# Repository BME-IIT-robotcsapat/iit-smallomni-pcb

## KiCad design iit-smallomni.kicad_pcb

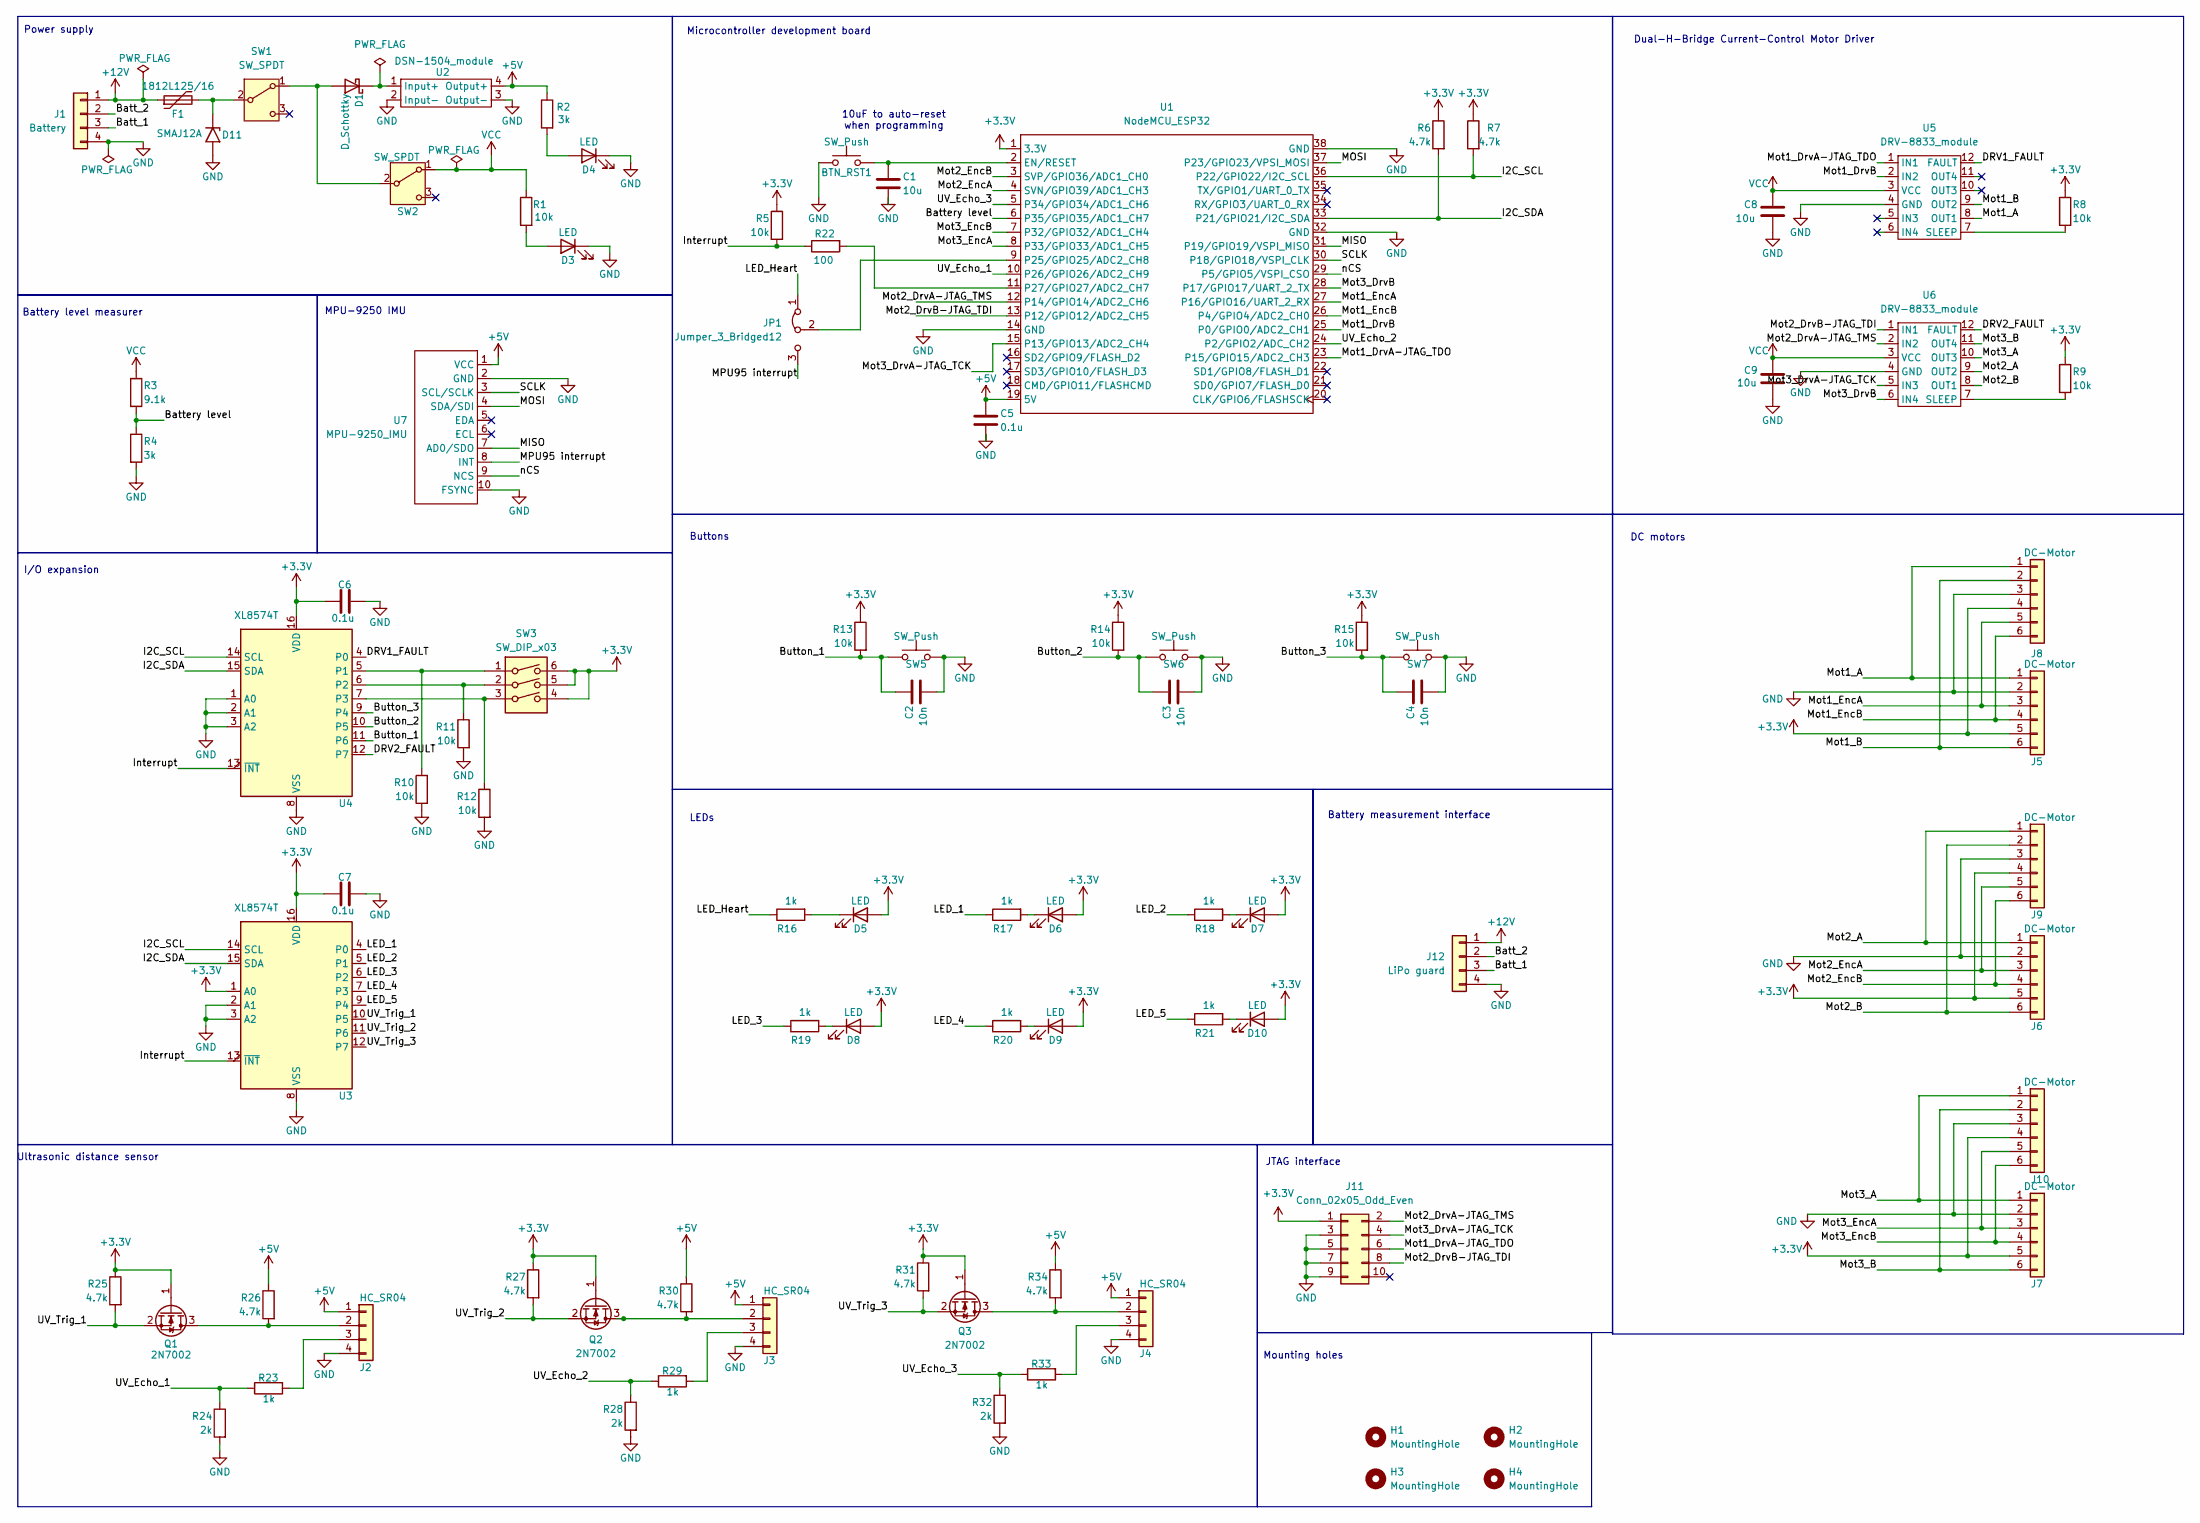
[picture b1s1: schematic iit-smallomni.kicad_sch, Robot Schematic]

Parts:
BTN_RST1: SW_Push; SW_PUSH_6mm_H5mm
C1, C8, C9: 10u; C_0805_2012Metric_Pad1.18x1.45mm_HandSolder
C2, C3, C4: 10n; C_0805_2012Metric_Pad1.18x1.45mm_HandSolder
C5, C6, C7: 0.1u; C_0805_2012Metric_Pad1.18x1.45mm_HandSolder
D1: D_Schottky; D_SOD-123FL
D3, D4, D5, D6, D7, D8, D9, D10: LED; LED_0805_2012Metric_Pad1.15x1.40mm_HandSolder
D11: SMAJ12A; D_SMA
F1: 1812L125/16; polyfuse
H1, H2, H3, H4: MountingHole; MountingHole_3.2mm_M3
J1: Battery; Molex_KK-254_AE-6410-04A_1x04_P2.54mm_Vertical
J2, J3, J4: HC_SR04; PinSocket_1x04_P2.54mm_Vertical
J5, J6, J7: DC-Motor; Molex_KK-254_AE-6410-06A_1x06_P2.54mm_Vertical
J8, J9, J10: DC-Motor; legacy-motor
J11: Conn_02x05_Odd_Even; IDC-Header_2x05_P2.54mm_Vertical
J12: LiPo guard; PinSocket_1x04_P2.54mm_Vertical
JP1: Jumper_3_Bridged12; PinHeader_1x03_P2.54mm_Vertical
Q1, Q2, Q3: 2N7002; SOT-23
R1, R5, R8, R9, R10, R11, R12, R13, R14, R15: 10k; R_0805_2012Metric_Pad1.20x1.40mm_HandSolder
R2, R4: 3k; R_0805_2012Metric_Pad1.20x1.40mm_HandSolder
R3: 9.1k; R_0805_2012Metric_Pad1.20x1.40mm_HandSolder
R6, R7, R25, R26, R27, R30, R31, R34: 4.7k; R_0805_2012Metric_Pad1.20x1.40mm_HandSolder
R16, R17, R18, R19, R20, R21, R23, R29, R33: 1k; R_0805_2012Metric_Pad1.20x1.40mm_HandSolder
R22: 100; R_0805_2012Metric_Pad1.20x1.40mm_HandSolder
R24, R28, R32: 2k; R_0805_2012Metric_Pad1.20x1.40mm_HandSolder
SW1, SW2: SW_SPDT; PinSocket_1x03_P2.54mm_Vertical
SW3: SW_DIP_x03; SW_DIP_SPSTx03_Slide_9.78x9.8mm_W7.62mm_P2.54mm
SW5, SW6, SW7: SW_Push; SW_PUSH_6mm_H5mm
U1: NodeMCU_ESP32; NodeMCU32S
U2: DSN-1504_module; DSN1504_module
U3, U4: XL8574T; SOIC-16W_7.5x10.3mm_P1.27mm
U5, U6: DRV-8833_module
U7: MPU-9250_IMU; PinSocket_1x10_P2.54mm_Vertical

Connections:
+3.3V: C6.1, C7.1, D5.2 (A), D6.2 (A), D7.2 (A), D8.2 (A), D9.2 (A), D10.2 (A), J5.5, J6.5, J7.5, J8.4, J9.4, J10.4, J11.1, Q1.1 (G), Q2.1 (G), Q3.1 (G), R5.1, R6.1, R7.1, R8.1, R9.1, R13.1, R14.1, R15.1, R25.1, R27.1, R31.1, SW3.4, SW3.5, SW3.6, U1.1 (3.3V), U3.1 (A0), U3.16 (VDD), U4.16 (VDD)
+5V: C5.1, J2.1, J3.1, J4.1, R2.1, R26.1, R30.1, R34.1, U1.19 (5V), U2.4 (Output+), U7.1 (VCC)
+12V: F1.1, J1.1, J12.1
/Batt_1: J1.3, J12.3
/Batt_2: J1.2, J12.2
/Battery level: R3.2, R4.1, U1.6 (P35/GPIO35/ADC1_CH7)
/Button_1: C2.1, R13.2, SW5.1, U4.11 (P6)
/Button_2: C3.1, R14.2, SW6.1, U4.10 (P5)
/Button_3: C4.1, R15.2, SW7.1, U4.9 (P4)
/DRV1_FAULT: U4.4 (P0), U5.12 (FAULT)
/DRV2_FAULT: U4.12 (P7), U6.12 (FAULT)
/I2C_SCL: R7.2, U1.36 (P22/GPIO22/I2C_SCL), U3.14 (SCL), U4.14 (SCL)
/I2C_SDA: R6.2, U1.33 (P21/GPIO21/I2C_SDA), U3.15 (SDA), U4.15 (SDA)
/Interrupt: R5.2, R22.1, U3.13 (~INT), U4.13 (~INT)
/LED_1: R17.1, U3.4 (P0)
/LED_2: R18.1, U3.5 (P1)
/LED_3: R19.1, U3.6 (P2)
/LED_4: R20.1, U3.7 (P3)
/LED_5: R21.1, U3.9 (P4)
/LED_Heart: JP1.1 (A), R16.1
/MISO: U1.31 (P19/GPIO19/VSPI_MISO), U7.7 (AD0/SDO)
/MOSI: U1.37 (P23/GPIO23/VPSI_MOSI), U7.4 (SDA/SDI)
/MPU95 interrupt: JP1.3 (B), U7.8 (INT)
/Mot1_A: J5.1, J8.1, U5.8 (OUT1)
/Mot1_B: J5.6, J8.2, U5.9 (OUT2)
/Mot1_DrvA-JTAG_TDO: J11.6, U1.23 (P15/GPIO15/ADC2_CH3), U5.1 (IN1)
/Mot1_DrvB: U1.25 (P0/GPIO0/ADC2_CH1), U5.2 (IN2)
/Mot1_EncA: J5.3, J8.5, U1.27 (P16/GPIO16/UART_2_RX)
/Mot1_EncB: J5.4, J8.6, U1.26 (P4/GPIO4/ADC2_CH0)
/Mot2_A: J6.1, J9.1, U6.9 (OUT2)
/Mot2_B: J6.6, J9.2, U6.8 (OUT1)
/Mot2_DrvA-JTAG_TMS: J11.2, U1.12 (P14/GPIO14/ADC2_CH6), U6.2 (IN2)
/Mot2_DrvB-JTAG_TDI: J11.8, U1.13 (P12/GPIO12/ADC2_CH5), U6.1 (IN1)
/Mot2_EncA: J6.3, J9.5, U1.4 (SVN/GPIO39/ADC1_CH3)
/Mot2_EncB: J6.4, J9.6, U1.3 (SVP/GPIO36/ADC1_CH0)
/Mot3_A: J7.1, J10.1, U6.10 (OUT3)
/Mot3_B: J7.6, J10.2, U6.11 (OUT4)
/Mot3_DrvA-JTAG_TCK: J11.4, U1.15 (P13/GPIO13/ADC2_CH4), U6.5 (IN3)
/Mot3_DrvB: U1.28 (P17/GPIO17/UART_2_TX), U6.6 (IN4)
/Mot3_EncA: J7.3, J10.5, U1.8 (P33/GPIO33/ADC1_CH5)
/Mot3_EncB: J7.4, J10.6, U1.7 (P32/GPIO32/ADC1_CH4)
/SCLK: U1.30 (P18/GPIO18/VSPI_CLK), U7.3 (SCL/SCLK)
/UV_Echo_1: R23.1, R24.1, U1.10 (P26/GPIO26/ADC2_CH9)
/UV_Echo_2: R28.1, R29.1, U1.24 (P2/GPIO2/ADC_CH2)
/UV_Echo_3: R32.1, R33.1, U1.5 (P34/GPIO34/ADC1_CH6)
/UV_Trig_1: Q1.2 (S), R25.2, U3.10 (P5)
/UV_Trig_2: Q2.2 (S), R27.2, U3.11 (P6)
/UV_Trig_3: Q3.2 (S), R31.2, U3.12 (P7)
/nCS: U1.29 (P5/GPIO5/VSPI_CSO), U7.9 (NCS)
GND: BTN_RST1.1, C1.2, C2.2, C3.2, C4.2, C5.2, C6.2, C7.2, C8.2, C9.2, D3.1 (K), D4.1 (K), D11.2 (A2), J1.4, J2.4, J3.4, J4.4, J5.2, J6.2, J7.2, J8.3, J9.3, J10.3, J11.3, J11.5, J11.7, J11.9, J12.4, R4.2, R10.2, R11.2, R12.2, R24.2, R28.2, R32.2, SW5.2, SW6.2, SW7.2, U1.14 (GND), U1.32 (GND), U1.38 (GND), U2.2 (Input-), U2.3 (Output-), U3.2 (A1), U3.3 (A2), U3.8 (VSS), U4.1 (A0), U4.2 (A1), U4.3 (A2), U4.8 (VSS), U5.4 (GND), U6.4 (GND), U7.2 (GND), U7.10 (FSYNC)
unnamed: D1.2 (A), SW1.1 (A), SW2.2 (B)
unnamed: D1.1 (K), U2.1 (Input+)
unnamed: D3.2 (A), R1.2
unnamed: D4.2 (A), R2.2
unnamed: D5.1 (K), R16.2
unnamed: D6.1 (K), R17.2
unnamed: D7.1 (K), R18.2
unnamed: D8.1 (K), R19.2
unnamed: D9.1 (K), R20.2
unnamed: D10.1 (K), R21.2
unnamed: D11.1 (A1), F1.2, SW1.2 (B)
unnamed: J2.2, Q1.3 (D), R26.2
unnamed: J2.3, R23.2
unnamed: J3.2, Q2.3 (D), R30.2
unnamed: J3.3, R29.2
unnamed: J4.2, Q3.3 (D), R34.2
unnamed: J4.3, R33.2
unnamed: JP1.2 (C), U1.9 (P25/GPIO25/ADC2_CH8)
unnamed: BTN_RST1.2, C1.1, U1.2 (EN/RESET)
unnamed: R22.2, U1.11 (P27/GPIO27/ADC2_CH7)
unnamed: R10.1, SW3.1, U4.5 (P1)
unnamed: R11.1, SW3.2, U4.6 (P2)
unnamed: R12.1, SW3.3, U4.7 (P3)
unnamed: R8.2, U5.7 (SLEEP)
unnamed: R9.2, U6.7 (SLEEP)
VCC: C8.1, C9.1, R1.1, R3.1, SW2.1 (A), U5.3 (VCC), U6.3 (VCC)

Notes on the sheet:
Ultrasonic distance sensor
Mounting holes
LEDs
I/O expansion
Power supply
DC motors
Microcontroller development board
10uF to auto-reset when programming
JTAG interface
MPU-9250 IMU
Dual-H-Bridge Current-Control Motor Driver
Battery level measurer
Buttons
Battery measurement interface

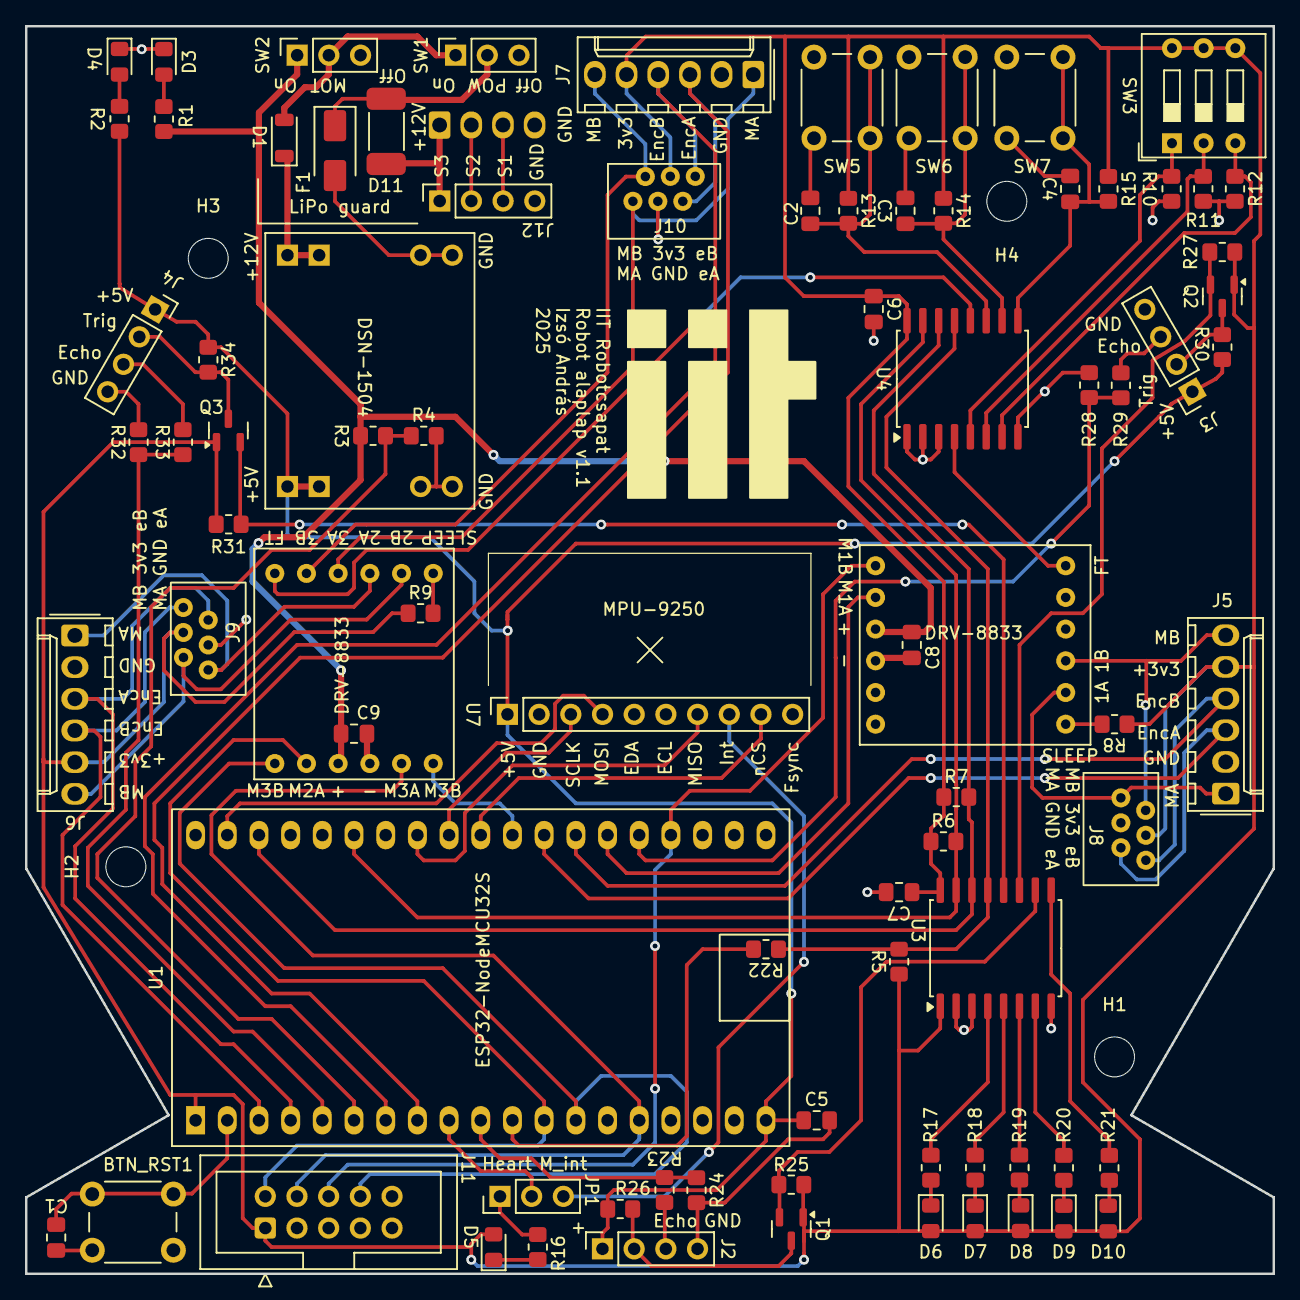
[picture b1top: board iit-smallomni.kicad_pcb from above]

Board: 2 copper layers, 100.0 x 100.0 mm, 88 parts (1 on the bottom side), 76 nets.

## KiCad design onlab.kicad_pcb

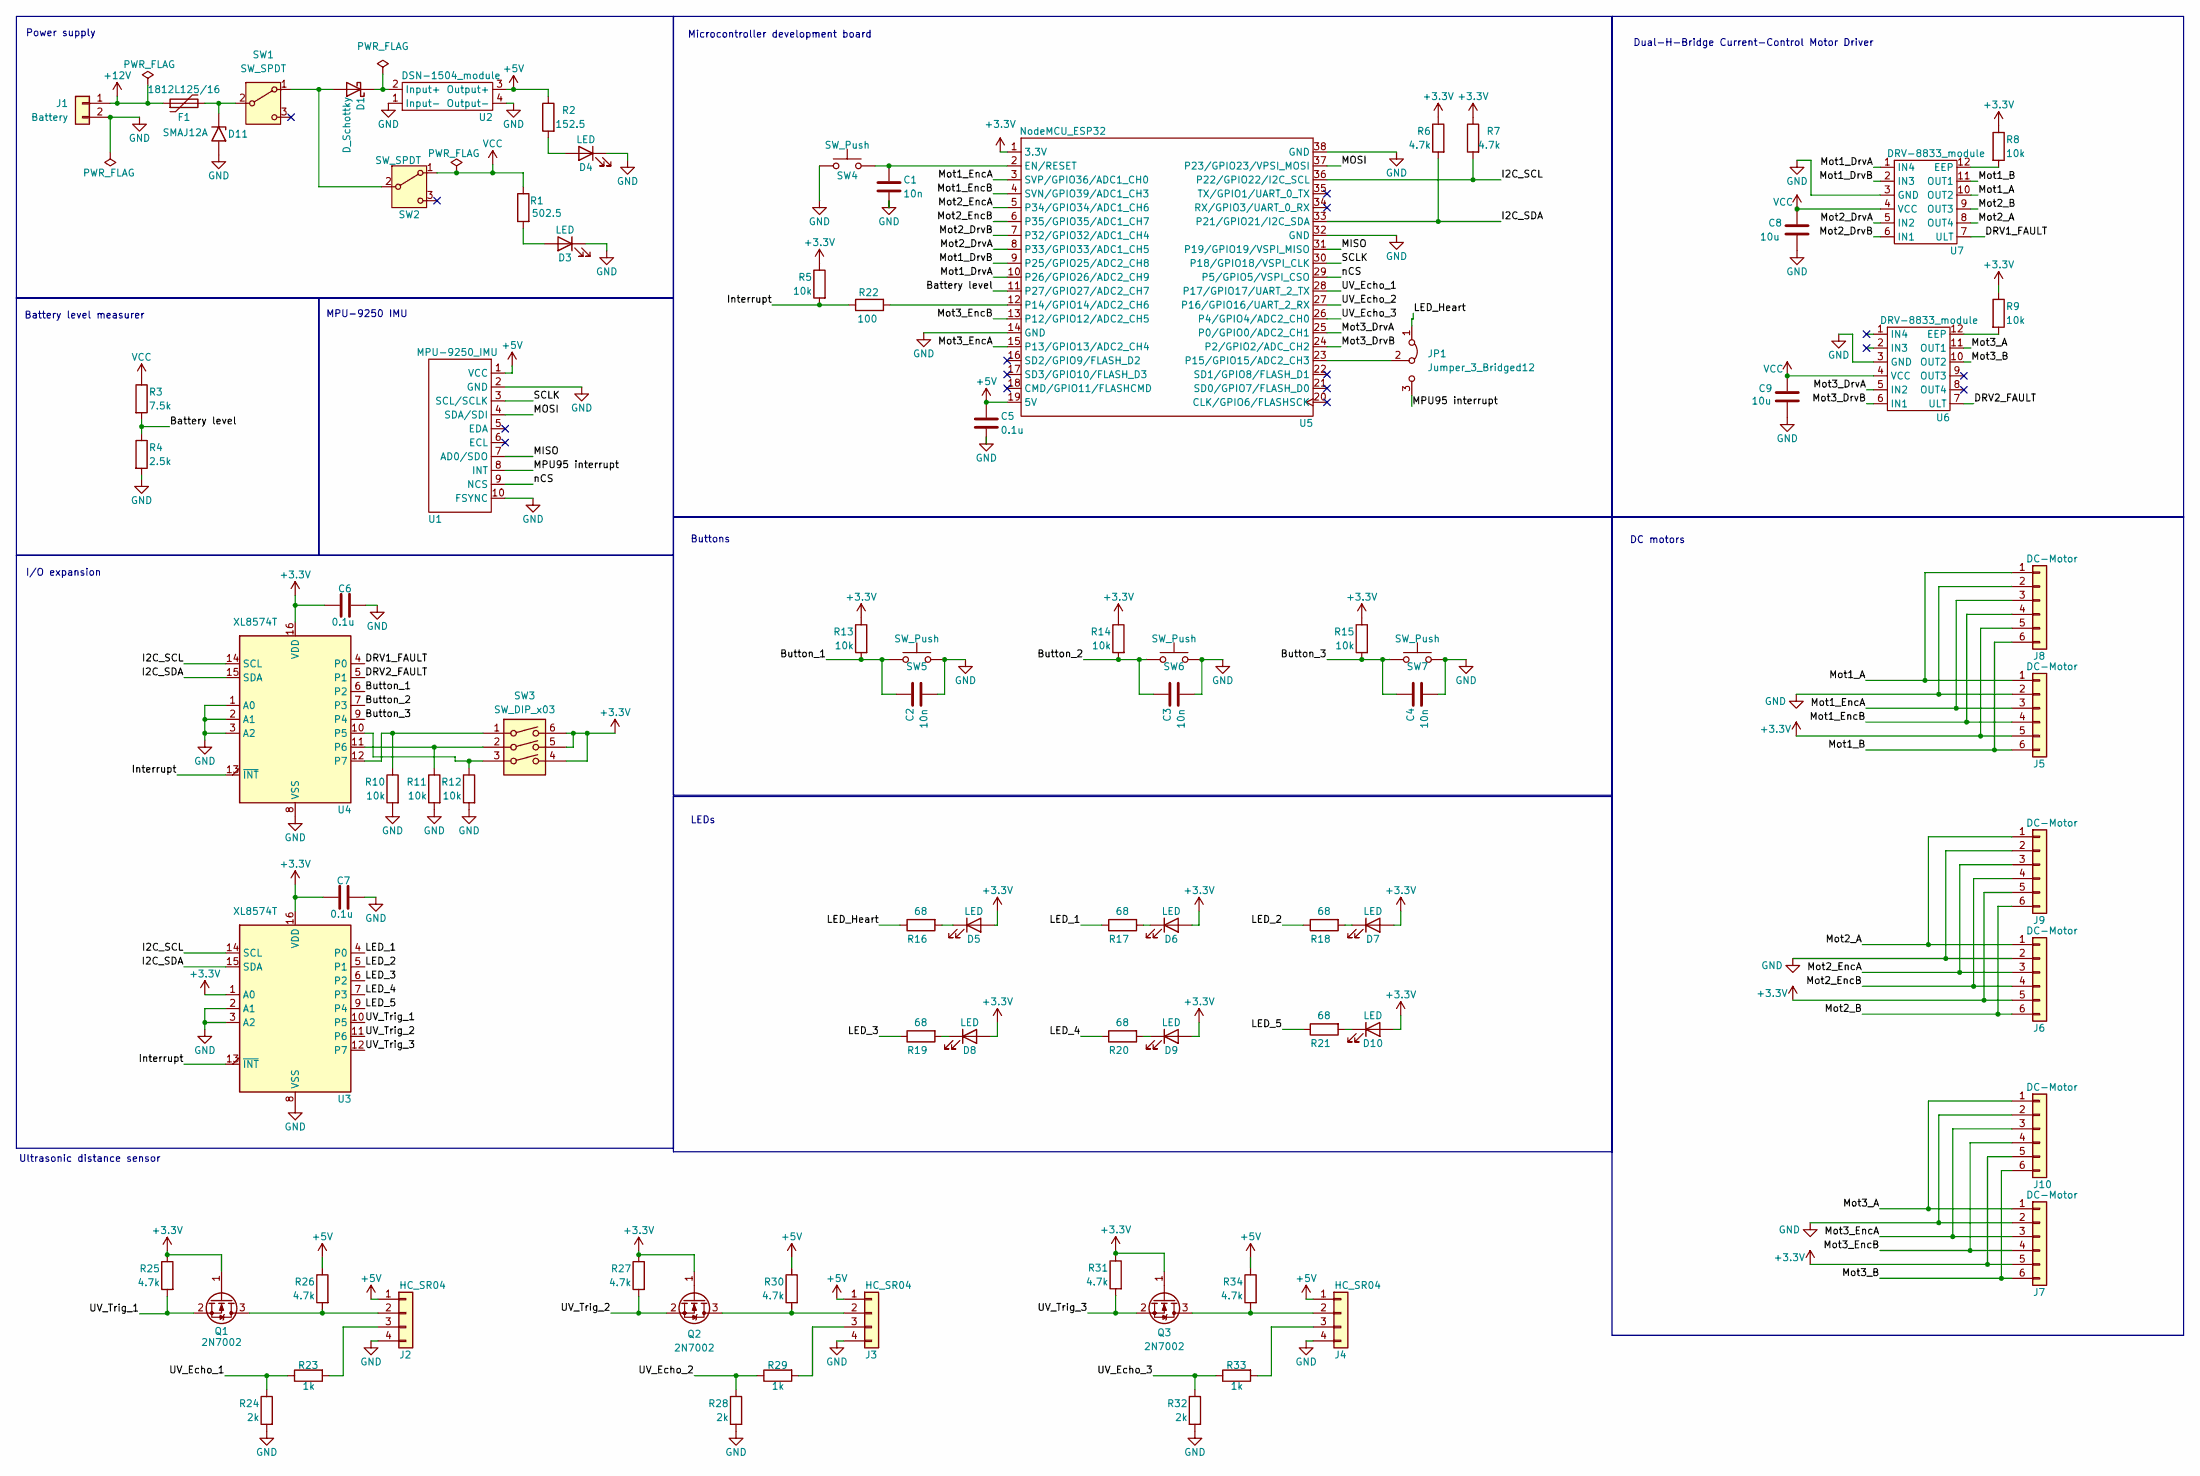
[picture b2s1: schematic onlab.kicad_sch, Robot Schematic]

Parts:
C1, C2, C3, C4: 10n; C_0805_2012Metric_Pad1.18x1.45mm_HandSolder
C5, C6, C7: 0.1u; C_0805_2012Metric_Pad1.18x1.45mm_HandSolder
C8, C9: 10u; C_0805_2012Metric_Pad1.18x1.45mm_HandSolder
D1: D_Schottky; D_0805_2012Metric_Pad1.15x1.40mm_HandSolder
D3, D4, D5, D6, D7, D8, D9, D10: LED; LED_0805_2012Metric_Pad1.15x1.40mm_HandSolder
D11: SMAJ12A; D_SMA
F1: 1812L125/16; polyfuse
J1: Battery; Molex_KK-254_AE-6410-02A_1x02_P2.54mm_Vertical
J2, J3, J4: HC_SR04; PinSocket_1x04_P2.54mm_Vertical
J5, J6, J7: DC-Motor; Molex_KK-254_AE-6410-06A_1x06_P2.54mm_Vertical
J8, J9, J10: DC-Motor; motor
JP1: Jumper_3_Bridged12; FanPinHeader_1x03_P2.54mm_Vertical
Q1, Q2, Q3: 2N7002; SOT-23
R1: 502.5; R_0805_2012Metric_Pad1.20x1.40mm_HandSolder
R2: 152.5; R_0805_2012Metric_Pad1.20x1.40mm_HandSolder
R3: 7.5k; R_0805_2012Metric_Pad1.20x1.40mm_HandSolder
R4: 2.5k; R_0805_2012Metric_Pad1.20x1.40mm_HandSolder
R5, R8, R9, R10, R11, R12, R13, R14, R15: 10k; R_0805_2012Metric_Pad1.20x1.40mm_HandSolder
R6, R7, R25, R26, R27, R30, R31, R34: 4.7k; R_0805_2012Metric_Pad1.20x1.40mm_HandSolder
R16, R17, R18, R19, R20, R21: 68; R_0805_2012Metric_Pad1.20x1.40mm_HandSolder
R22: 100; R_0805_2012Metric_Pad1.20x1.40mm_HandSolder
R23, R29, R33: 1k; R_0805_2012Metric_Pad1.20x1.40mm_HandSolder
R24, R28, R32: 2k; R_0805_2012Metric_Pad1.20x1.40mm_HandSolder
SW1, SW2: SW_SPDT; FanPinHeader_1x03_P2.54mm_Vertical
SW3: SW_DIP_x03; SW_DIP_SPSTx03_Slide_9.78x9.8mm_W7.62mm_P2.54mm
SW4, SW5, SW6, SW7: SW_Push; SW_PUSH_6mm_H5mm
U1: MPU-9250_IMU; PinSocket_1x10_P2.54mm_Vertical
U2: DSN-1504_module; DSN1504_module
U3, U4: XL8574T; SOIC-16W_7.5x10.3mm_P1.27mm
U5: NodeMCU_ESP32; MODULE_NODEMCU-32S
U6, U7: DRV-8833_module

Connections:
+3.3V: C6.1, C7.1, D5.2 (A), D6.2 (A), D7.2 (A), D8.2 (A), D9.2 (A), D10.2 (A), J5.5, J6.5, J7.5, J8.5, J9.5, J10.5, Q1.1 (G), Q2.1 (G), Q3.1 (G), R5.1, R6.1, R7.1, R8.1, R9.1, R13.1, R14.1, R15.1, R25.1, R27.1, R31.1, SW3.4, SW3.5, SW3.6, U3.1 (A0), U3.16 (VDD), U4.16 (VDD), U5.1 (3.3V)
+5V: C5.1, J2.1, J3.1, J4.1, R2.1, R26.1, R30.1, R34.1, U1.1 (VCC), U2.3 (Output+), U5.19 (5V)
+12V: F1.1, J1.1
/Battery level: R3.2, R4.1, U5.11 (P27/GPIO27/ADC2_CH7)
/Button_1: C2.1, R13.2, SW5.1, U4.6 (P2)
/Button_2: C3.1, R14.2, SW6.1, U4.7 (P3)
/Button_3: C4.1, R15.2, SW7.1, U4.9 (P4)
/DRV1_FAULT: U4.4 (P0), U7.7 (ULT)
/DRV2_FAULT: U4.5 (P1), U6.7 (ULT)
/I2C_SCL: R7.2, U3.14 (SCL), U4.14 (SCL), U5.36 (P22/GPIO22/I2C_SCL)
/I2C_SDA: R6.2, U3.15 (SDA), U4.15 (SDA), U5.33 (P21/GPIO21/I2C_SDA)
/Interrupt: R5.2, R22.1, U3.13 (~INT), U4.13 (~INT)
/LED_1: R17.1, U3.4 (P0)
/LED_2: R18.1, U3.5 (P1)
/LED_3: R19.1, U3.6 (P2)
/LED_4: R20.1, U3.7 (P3)
/LED_5: R21.1, U3.9 (P4)
/LED_Heart: JP1.1 (A), R16.1
/MISO: U1.7 (AD0/SDO), U5.31 (P19/GPIO19/VSPI_MISO)
/MOSI: U1.4 (SDA/SDI), U5.37 (P23/GPIO23/VPSI_MOSI)
/MPU95 interrupt: JP1.3 (B), U1.8 (INT)
/Mot1_A: J5.1, J8.1, U7.10 (OUT2)
/Mot1_B: J5.6, J8.6, U7.11 (OUT1)
/Mot1_DrvA: U5.10 (P26/GPIO26/ADC2_CH9), U7.1 (IN4)
/Mot1_DrvB: U5.9 (P25/GPIO25/ADC2_CH8), U7.2 (IN3)
/Mot1_EncA: J5.3, J8.3, U5.3 (SVP/GPIO36/ADC1_CH0)
/Mot1_EncB: J5.4, J8.4, U5.4 (SVN/GPIO39/ADC1_CH3)
/Mot2_A: J6.1, J9.1, U7.8 (OUT4)
/Mot2_B: J6.6, J9.6, U7.9 (OUT3)
/Mot2_DrvA: U5.8 (P33/GPIO33/ADC1_CH5), U7.5 (IN2)
/Mot2_DrvB: U5.7 (P32/GPIO32/ADC1_CH4), U7.6 (IN1)
/Mot2_EncA: J6.3, J9.3, U5.5 (P34/GPIO34/ADC1_CH6)
/Mot2_EncB: J6.4, J9.4, U5.6 (P35/GPIO35/ADC1_CH7)
/Mot3_A: J7.1, J10.1, U6.11 (OUT1)
/Mot3_B: J7.6, J10.6, U6.10 (OUT2)
/Mot3_DrvA: U5.25 (P0/GPIO0/ADC2_CH1), U6.5 (IN2)
/Mot3_DrvB: U5.24 (P2/GPIO2/ADC_CH2), U6.6 (IN1)
/Mot3_EncA: J7.3, J10.3, U5.15 (P13/GPIO13/ADC2_CH4)
/Mot3_EncB: J7.4, J10.4, U5.13 (P12/GPIO12/ADC2_CH5)
/SCLK: U1.3 (SCL/SCLK), U5.30 (P18/GPIO18/VSPI_CLK)
/UV_Echo_1: R23.1, R24.1, U5.28 (P17/GPIO17/UART_2_TX)
/UV_Echo_2: R28.1, R29.1, U5.27 (P16/GPIO16/UART_2_RX)
/UV_Echo_3: R32.1, R33.1, U5.26 (P4/GPIO4/ADC2_CH0)
/UV_Trig_1: Q1.2 (S), R25.2, U3.10 (P5)
/UV_Trig_2: Q2.2 (S), R27.2, U3.11 (P6)
/UV_Trig_3: Q3.2 (S), R31.2, U3.12 (P7)
/nCS: U1.9 (NCS), U5.29 (P5/GPIO5/VSPI_CSO)
GND: C1.2, C2.2, C3.2, C4.2, C5.2, C6.2, C7.2, C8.2, C9.2, D3.1 (K), D4.1 (K), D11.2 (A2), J1.2, J2.4, J3.4, J4.4, J5.2, J6.2, J7.2, J8.2, J9.2, J10.2, R4.2, R10.2, R11.2, R12.2, R24.2, R28.2, R32.2, SW4.1, SW5.2, SW6.2, SW7.2, U1.2 (GND), U1.10 (FSYNC), U2.1 (Input-), U2.4 (Output-), U3.2 (A1), U3.3 (A2), U3.8 (VSS), U4.1 (A0), U4.2 (A1), U4.3 (A2), U4.8 (VSS), U5.14 (GND), U5.32 (GND), U5.38 (GND), U6.3 (GND), U7.3 (GND)
unnamed: D1.2 (A), SW1.1 (A), SW2.2 (B)
unnamed: D1.1 (K), U2.2 (Input+)
unnamed: D3.2 (A), R1.2
unnamed: D4.2 (A), R2.2
unnamed: D5.1 (K), R16.2
unnamed: D6.1 (K), R17.2
unnamed: D7.1 (K), R18.2
unnamed: D8.1 (K), R19.2
unnamed: D9.1 (K), R20.2
unnamed: D10.1 (K), R21.2
unnamed: D11.1 (A1), F1.2, SW1.2 (B)
unnamed: J2.2, Q1.3 (D), R26.2
unnamed: J2.3, R23.2
unnamed: J3.2, Q2.3 (D), R30.2
unnamed: J3.3, R29.2
unnamed: J4.2, Q3.3 (D), R34.2
unnamed: J4.3, R33.2
unnamed: JP1.2 (C), U5.23 (P15/GPIO15/ADC2_CH3)
unnamed: R12.1, SW3.3, U4.10 (P5)
unnamed: R11.1, SW3.2, U4.11 (P6)
unnamed: R10.1, SW3.1, U4.12 (P7)
unnamed: C1.1, SW4.2, U5.2 (EN/RESET)
unnamed: R22.2, U5.12 (P14/GPIO14/ADC2_CH6)
unnamed: R9.2, U6.12 (EEP)
unnamed: R8.2, U7.12 (EEP)
VCC: C8.1, C9.1, R1.1, R3.1, SW2.1 (A), U6.4 (VCC), U7.4 (VCC)

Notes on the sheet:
Ultrasonic distance sensor
LEDs
I/O expansion
Power supply
DC motors
Microcontroller development board
MPU-9250 IMU
Dual-H-Bridge Current-Control Motor Driver
Battery level measurer
Buttons

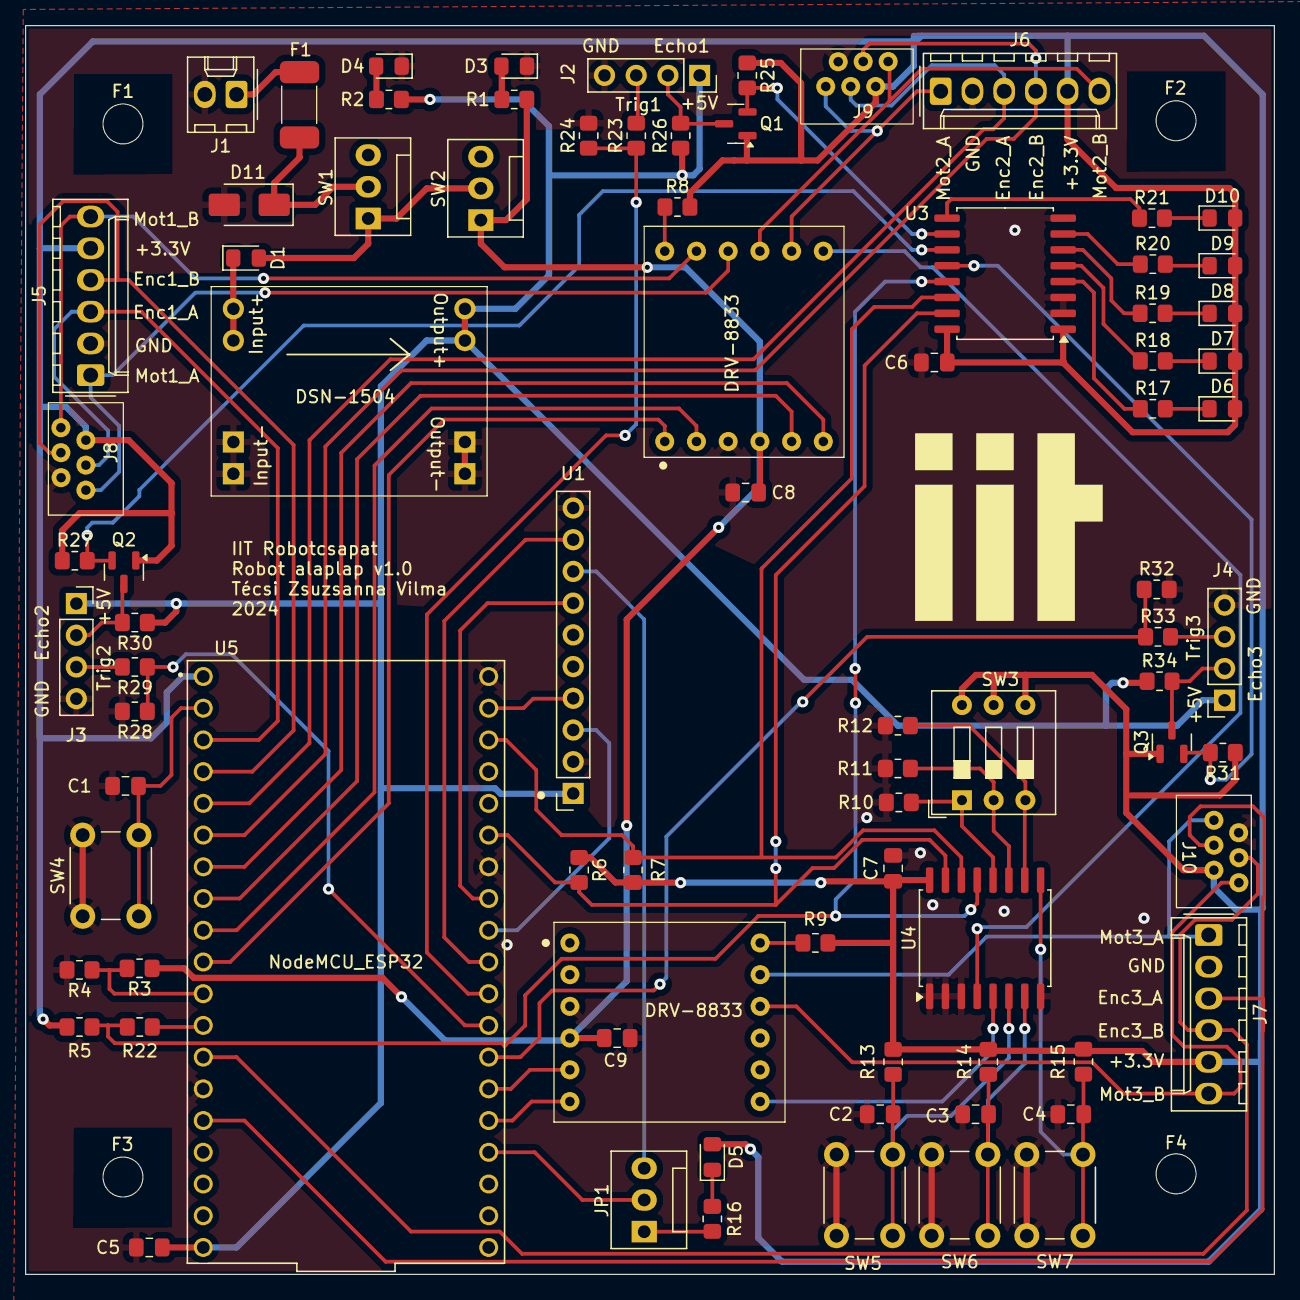
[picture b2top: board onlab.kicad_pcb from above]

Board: 2 copper layers, 100.0 x 100.0 mm, 86 parts (0 on the bottom side), 74 nets.

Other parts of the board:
F1#2, F2, F3, F4: MountingHole_3.2mm_M3

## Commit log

2024-02-25 init
2024-04-30 first upload
2024-05-16 Schematic and footprint update
2024-05-16 resistor value
2024-05-20 schematic update
2024-05-20 schematic update: dc motor connectors
2024-09-04 footprint assignment final
2024-09-09 motor footprint update
2024-09-14 layout v2
2024-09-15 Routing
2024-09-16 Routing part 2
2024-09-16 Routing part 3 - remain to be done motors and vcc
2024-09-16 Routing part 4 - remain to be done GND and GNDPWR
2024-09-18 Layout finish
2024-09-18 schematic and layout pdf
2024-09-23 Correction of schematic and layout
2024-09-24 Correction of Q1, Q2, Q3 and update of libraries
2024-09-25 keep out area update, pdf update
2024-10-04 resistor value update
2024-10-04 resistor value update 2
2025-07-06 Clean up names, schematic grid and files
2025-07-06 Change reset capacitor to 10uF
2025-07-06 Fix flipped DRV8833
2025-07-06 Fix flipped DSN-1504
2025-07-06 Create footprint for Schottky diode (SOD-123FL)
2025-07-06 Update Schottky diode footprint in design
2025-07-06 Fix motor connector layout
2025-07-06 Fix MPU9250 orientation
2025-07-06 JTAG, LiPo guard, Mounting hole
2025-07-08 Edge & basic layout
2025-07-15 Routing refinement around esp and i2c
2025-07-16 All routed except GND
2025-07-17 Routing done, ERC & DRC errors eliminated
2025-07-17 JTAG signal naming fixed
2025-07-17 Tidy up silkscreen, eliminate warnings
2025-07-17 Add pin annotations
2025-07-17 Update schematic export
2025-07-17 Fix pdf export
2025-07-17 Add annotation for esp32
